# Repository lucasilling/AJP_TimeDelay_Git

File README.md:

# AJP Time Delay Device Documentation

Supplemental material for article on a programmable electronic delay circuit.

- `assembly-instructions`: A guide to ordering parts and building the device
  yourself.

- `arduino/FIFO_P`: The code uploaded to the Arduino Due.

- `fifo-p3f`: The KiCAD files for the device, as well as a schematic
  PDF and the gerber files that I sent for manufacture.

- `program-rescaling`: The code used to calculate the gain and offset
  resistor values to be optimal, given the constraints of E-series
  values and the overall resistances needed.

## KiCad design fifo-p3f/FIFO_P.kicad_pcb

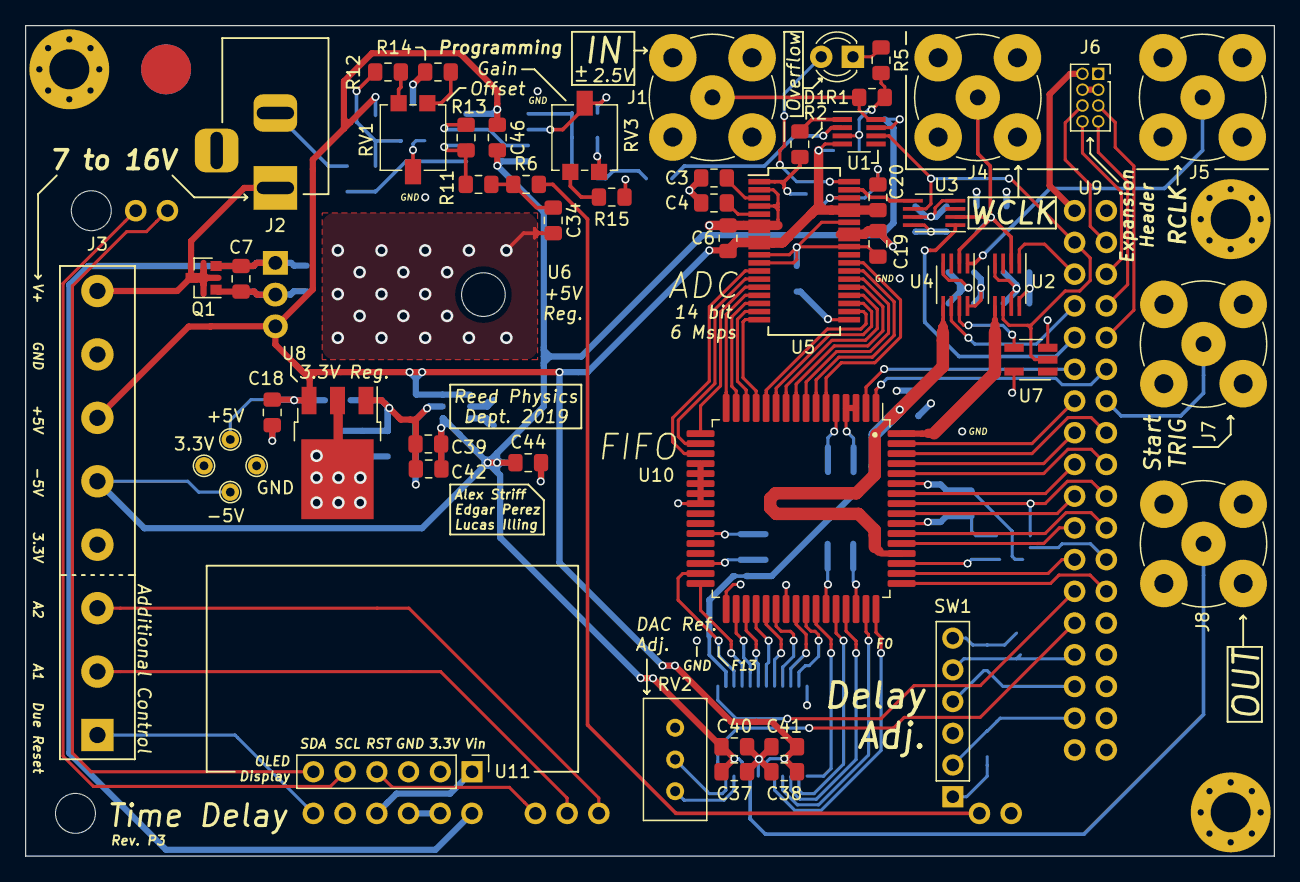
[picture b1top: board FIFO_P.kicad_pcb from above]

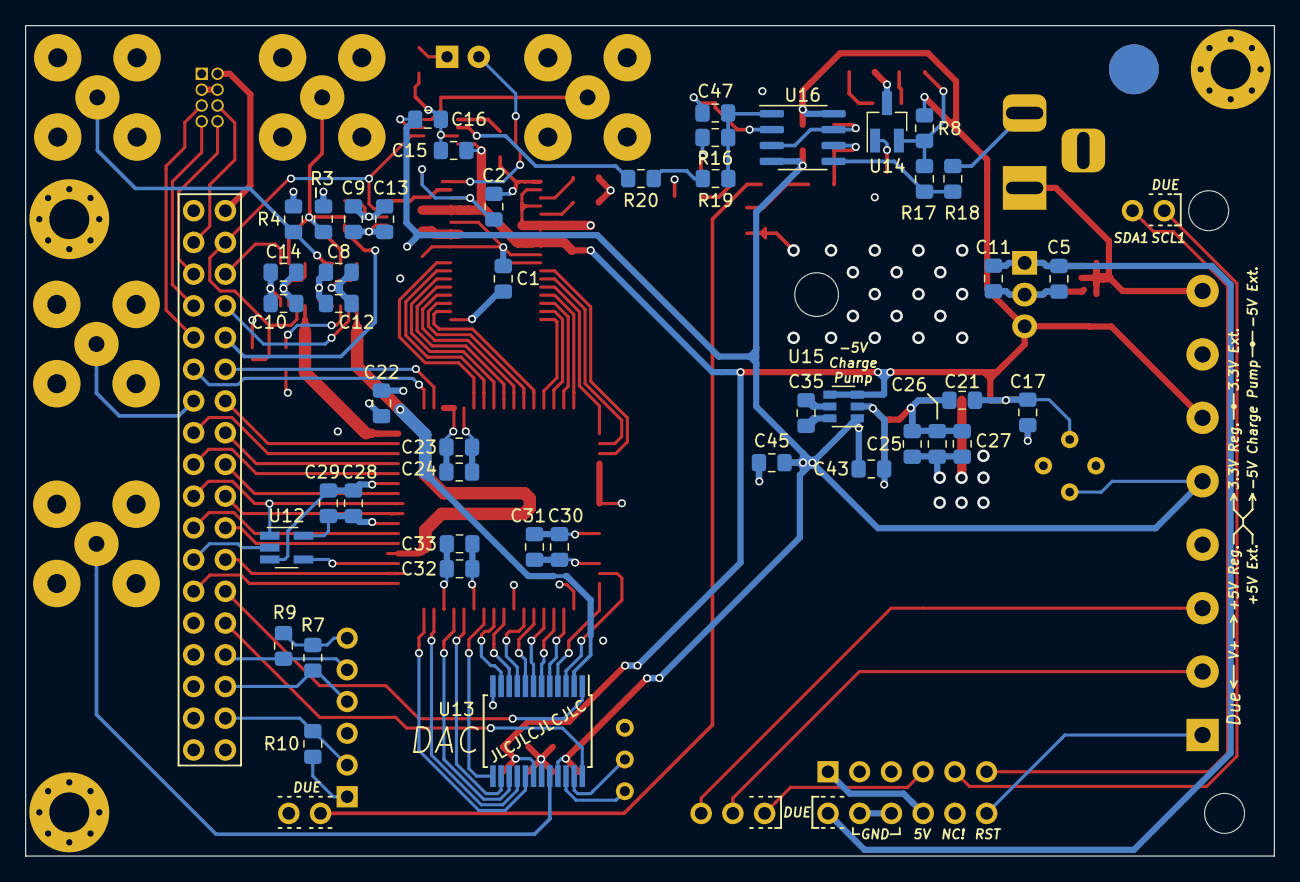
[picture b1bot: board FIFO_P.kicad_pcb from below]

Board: 4 copper layers, 100.0 x 66.5 mm, 100 parts (46 on the bottom side), 104 nets.

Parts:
C1, C3, C4, C6, C11, C12, C13, C14, C19, C20, C21, C25, C35, C39, C40, C41: 1u; C_0805_2012Metric_Pad1.15x1.40mm_HandSolder
C2, C34, C47: 1n; C_0805_2012Metric_Pad1.15x1.40mm_HandSolder
C5, C7, C17, C18, C24, C26, C27, C29, C31, C33, C42, C43, C44, C45: 10u; C_0805_2012Metric_Pad1.15x1.40mm_HandSolder
C8, C9, C10, C15, C16, C22, C23, C28, C30, C32, C37, C38, C46: 0u1; C_0805_2012Metric_Pad1.15x1.40mm_HandSolder
D1: LED_RED; LED_D3.0mm
J1: Vin; BNC_TEConnectivity_1478204_Vertical
J2: Jack-DC; BarrelJack_Horizontal
J3: Screw_Terminal_01x08; TerminalBlock_Phoenix_MKDS-3-8-5.08_1x08_P5.08mm_Horizontal
J4: XWCLK; BNC_TEConnectivity_1478204_Vertical
J5: XRCLK; BNC_TEConnectivity_1478204_Vertical
J6: Conn_02x04_Odd_Even; PinSocket_2x04_P1.27mm_Vertical
J7: Start Trigger; BNC_TEConnectivity_1478204_Vertical
J8: Vout; BNC_TEConnectivity_1478204_Vertical
Q1: DMP3099L; SOT-23
R1, R3, R4, R19: 49R9; R_0805_2012Metric_Pad1.15x1.40mm_HandSolder
R2, R6, R20: 22R; R_0805_2012Metric_Pad1.15x1.40mm_HandSolder
R5: 220R; R_0805_2012Metric_Pad1.15x1.40mm_HandSolder
R7, R9, R10, R11, R13, R16, R17, R18: 5k1; R_0805_2012Metric_Pad1.15x1.40mm_HandSolder
R8, R14: 1k1; R_0805_2012Metric_Pad1.15x1.40mm_HandSolder
R12: 4k3; R_0805_2012Metric_Pad1.15x1.40mm_HandSolder
R15: 3k9; R_0805_2012Metric_Pad1.15x1.40mm_HandSolder
RV1, RV3: 1k; Potentiometer_Vishay_TS53YL_Vertical
RV2: 10k; Potentiometer_Bourns_3296W_Vertical
SW1: Rotary_Encoder_61C
TP1: GND; Test_Pin
TP2: +5V; Test_Pin
TP3: -5V; Test_Pin
TP4: 3.3V; Test_Pin
U1: TS12A12511; SOT-23-8_Handsoldering
U2, U3, U4: SN74LVC2G157_MUX_TI; SSOP-8_2.95x2.8mm_P0.65mm
U5: LTC1740; SSOP-36_5.3mm_Pitch0.65mm
U6: LM2940CT-5.0; TO-220-3_Horizontal_TabDown
U7: 74LVC1G04; SOT-23-5_HandSoldering
U8: LM1117-3.3; TO-252-3_TabPin2
U9: ARDUINO_DUE_FIFO_P_COMMANDS; Arduino_Due_Selected_Pins
U10: IDT_72V2105; LQFP-64_14x14mm_P0.8mm_HandSolder
U11: Adafruit_128x32_OLED_I2C_1306
U12: 74LVC1G08; SOT-23-5_HandSoldering
U13: AD7840; SSOP-24_5.3x8.2mm_P0.65mm
U14: LM4041LP-ADJ; SOT-23_Handsoldering
U15: LM2776; SOT-23-6
U16: TL082; SOIC-8_3.9x4.9mm_P1.27mm

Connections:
1CLK: U4.6, U9.D26
3.3V: C1.2, C8.1, C9.1, C10.1, C12.1, C13.1, C14.1, C22.1, C23.1, C24.1, C25.1, C26.1, C27.1, C28.1, C29.1, C30.1, C31.1, C32.2, C33.2, J3.4, J6.1, R7.1, R9.1, SW1.3, SW1.6, TP4.1, U2.8, U3.8, U4.8, U5.19, U7.5, U8.2, U10.3, U10.4, U10.30, U10.43, U10.55, U12.5
+5V: C6.2, C15.1, C17.1, C18.1, C20.2, C21.1, C38.2, C41.2, C46.1, J3.6, R8.2, TP2.1, U1.4, U5.8, U5.9, U5.32, U5.33, U6.3, U8.3, U13.18, U15.3, U15.4, U16.8
-5V: C16.2, C19.2, C37.1, C39.1, C40.1, C42.1, C43.1, C44.1, C45.1, C46.2, J3.5, TP3.1, U1.7, U5.29, U5.30, U13.21, U15.1, U16.4
/D0: U5.26, U10.6
/D1: U5.25, U10.7
/D2: U5.24, U10.8
/D3: U5.23, U10.9
/D4: U5.22, U10.10
/D5: U5.21, U10.11
/D6: U5.20, U10.12
/D7: U5.18, U10.13
/D8: U5.17, U10.14
/D9: U5.16, U10.15
/D10: U5.15, U10.16
/D11: U5.14, U10.17
/D12: U5.13, U10.18
/D13: U5.12, U10.19
/F0: U10.48, U13.17
/F1: U10.47, U13.16
/F2: U10.45, U13.15
/F3: U10.44, U13.14
/F4: U10.42, U13.13
/F5: U10.41, U13.11
/F6: U10.40, U13.10
/F7: U10.38, U13.9
/F8: U10.37, U13.8
/F9: U10.36, U13.7
/F10: U10.35, U13.6
/F11: U10.34, U13.5
/F12: U10.32, U13.4
/F13: U10.31, U13.3
A1: J3.2, U9.A1
A2: J3.3, U9.A2
ADC_CLK: U3.5, U5.35
ADC_CLK_S: U3.1, U9.D28
GND: C1.1, C2.1, C3.1, C4.2, C5.2, C6.1, C7.2, C8.2, C9.2, C10.2, C11.2, C12.2, C13.2, C14.2, C15.2, C16.1, C17.2, C18.2, C19.1, C20.1, C21.2, C22.2, C23.2, C24.2, C25.2, C26.2, C27.2, C28.2, C29.2, C30.2, C31.2, C32.1, C33.1, C34.2, C37.2, C38.1, C39.2, C40.2, C41.1, C42.2, C43.2, C44.2, C45.2, J1.2, J2.2, J3.7, J4.2, J5.2, J6.3, J6.4, J7.2, J8.2, Q1.1, R1.1, R3.2, R4.2, R5.2, R10.1, R14.2, R15.2, R17.2, RV2.3, SW1.1, TP1.1, U1.3, U2.4, U2.7, U3.4, U3.7, U4.4, U5.2, U5.4, U5.6, U5.7, U5.10, U5.11, U5.28, U5.31, U5.34, U6.2, U7.3, U8.1, U9.GND2, U9.GND3, U10.5, U10.20, U10.21, U10.22, U10.23, U10.24, U10.27, U10.33, U10.39, U10.46, U10.59, U11.3, U12.3, U13.12, U13.19, U14.3, U15.2
unnamed: C2.2, R2.1, U5.1
unnamed: C3.2, U5.3
unnamed: C4.1, U5.5
unnamed: C34.1, R6.1, R11.2
unnamed: C35.1, U15.6
unnamed: C35.2, U15.5
unnamed: C47.1, R16.1, R19.2, U16.1
unnamed: C47.2, RV3.2, U16.2
unnamed: D1.1, R5.1
unnamed: D1.2, U5.36
unnamed: J1.1, R1.2, U1.8
unnamed: J2.1, J3.8, Q1.3
unnamed: J6.2, U9.5V3
unnamed: J6.5, U9.D29
unnamed: J6.6, U9.D23
unnamed: J6.7, U9.D27
unnamed: J6.8, U9.D25
unnamed: J7.1, U9.D33
unnamed: J8.1, U13.20
unnamed: R2.2, U1.1
unnamed: R7.2, SW1.4, U9.D50
unnamed: R9.2, SW1.5, U9.D48
unnamed: R10.2, SW1.2, U9.D52
unnamed: R11.1, R13.2, U16.6
unnamed: R8.1, R12.1, R18.1, U14.2
unnamed: R12.2, RV1.1
unnamed: R13.1, U16.3, U16.7
unnamed: R14.1, RV1.3
unnamed: R15.1, RV3.3
unnamed: R16.2, RV3.1
unnamed: R17.1, R18.2, U16.5
unnamed: R19.1, R20.2
unnamed: RV1.2, U14.1
unnamed: RV2.1, U13.22
unnamed: RV2.2, U13.23
unnamed: U9.D31, U10.1
unnamed: U9.D30, U10.2
unnamed: U9.D45, U10.49
unnamed: U9.D42, U10.50
unnamed: U10.51, U12.4
unnamed: U9.D40, U10.53
unnamed: U9.D41, U10.54
unnamed: U9.D38, U10.56
unnamed: U9.D39, U10.57, U12.1
unnamed: U9.D36, U10.58
unnamed: U9.D37, U10.60
unnamed: U9.D34, U10.61
unnamed: U9.D35, U10.62
unnamed: U9.D32, U10.63
unnamed: U9.5V1, U11.1
unnamed: U9.A0, U11.4
unnamed: U9.SCL1, U11.5
unnamed: U9.SDA1, U11.6
unnamed: U9.D43, U12.2
unnamed: U9.D44, U13.1
unnamed: U9.D46, U13.24
PROG: U4.7, U7.4
PROG_ADC: R20.1, U1.2
PROG_D: R6.2, U9.DAC1
RCLK: U4.5, U10.52, U13.2
RST1: J3.1, U9.RST1
V+: C5.1, C7.1, C11.1, Q1.2, U6.1, U9.VIN
WCLK: U2.5, U10.64
WCLK_S: U2.1, U9.D24
XRCLK: J5.1, R4.1, U4.1
XWCLK: J4.1, R3.1, U2.2, U3.2, U4.2
~PROG: U1.6, U2.6, U3.6, U7.2, U9.D22

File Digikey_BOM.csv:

Manufacturer Part Number,Manufacturer,Digi-Key Part Number,Customer Reference,Reference Designator,Packaging,Part Status,Quantity,Unit Price,Extended Price,Quantity Available,Mfg Std Lead Time,Description,RoHS Status,Lead Free Status,REACH Status
LM2940CT-5.0/NOPB,Texas Instruments,LM2940CT-5.0/NOPB-ND,,U6,Tube,Active,1,1.53,$1.53,7476,6 Weeks,IC REG LINEAR 5V 1A TO220-3,ROHS3 Compliant,Lead free,REACH Unaffected
LM2776DBVR,Texas Instruments,296-43957-1-ND,,U15,Cut Tape (CT),Active,1,1.02,$1.02,12481,6 Weeks,IC REG CHARGE PUMP INV SOT23,ROHS3 Compliant,Lead free,REACH Unaffected
AD7840ARSZ,Analog Devices Inc.,AD7840ARSZ-ND,,U13,Tube,Active,1,33.39,$33.39,643,8 Weeks,IC DAC 14BIT V-OUT 24SSOP,ROHS3 Compliant,Lead free,REACH Unaffected
72V2105L10PFG,Renesas Electronics America Inc.,800-1511-ND,,U10,Tray,Active,1,131.65,$131.65,45,13 Weeks,IC FIFO SUPERSYNC 10NS 64-TQFP,ROHS3 Compliant,Lead free,REACH Unaffected
LTC1740CG#PBF,Linear Technology/Analog Devices,LTC1740CG#PBF-ND,,U5,Tube,Active,1,41.67,$41.67,53,8 Weeks,IC ADC 14BIT PIPELINED 36SSOP,ROHS3 Compliant,Lead free,REACH Unaffected
SN74LVC2G157DCTR,Texas Instruments,296-13266-1-ND,,U2,Cut Tape (CT),Active,3,0.48,$1.44,3725,6 Weeks,IC 2-1LINE DATA SELECT/MUX SM8,ROHS3 Compliant,Lead free,REACH Unaffected
61C11-01-08-02,Grayhill Inc.,GH6102-ND,,SW1,Bulk,Active,1,25.77,$25.77,559,16 Weeks,ROTARY ENCODER OPTICAL 32PPR,RoHS non-compliant,Contains lead,REACH Unaffected
PRPC002SAAN-RC,Sullins Connector Solutions,S1011EC-02-ND,Board to board,U9,Bag,Active,2,0.08,$0.16,34630,Not Available,CONN HEADER VERT 2POS 2.54MM,ROHS3 Compliant,Lead free,REACH Unaffected
PJ-002A,CUI Devices,CP-002A-ND,,J2,Bag,Active,1,0.6,$0.60,35575,11 Weeks,CONN PWR JACK 2X5.5MM SOLDER,RoHS Compliant,Lead free,Not Available
151033RS03000,Würth Elektronik,732-5013-ND,,D1,Bulk,Active,1,0.17,$0.17,13557,14 Weeks,LED RED CLEAR 3MM ROUND T/H,ROHS3 Compliant,Lead free,REACH Unaffected
931,Adafruit Industries LLC,1528-1169-ND,128x32 OLED,U11,Bulk,Active,1,17.5,$17.50,357,2 Weeks,DISPL OLED GRAPH MONO 128X32 I2C,ROHS3 Compliant,Lead free,Not Available
A000062,Arduino,1050-1049-ND,,U9,Box,Active,1,37.4,$37.40,653,Not Available,ARDUINO DUE ATSAM3X8E EVAL BRD,RoHS Compliant,Lead free,Not Available
5-1634503-1,TE Connectivity AMP Connectors,A97581-ND,,"J1, J4, J5, J7, J8",Box,Active,5,2.25,$11.25,11968,Not Available,CONN BNC JACK STR 50 OHM PCB,RoHS Compliant,Lead free,Not Available
TS12A12511DCNR,Texas Instruments,296-27523-1-ND,,U1,Cut Tape (CT),Active,1,1.45,$1.45,11236,6 Weeks,IC SWITCH SGL SPDT ANLG SOT23-8,ROHS3 Compliant,Lead free,REACH Unaffected
LM4041DYM3-ADJ-TR,Microchip Technology,576-2573-1-ND,,U14,Cut Tape (CT),Active,1,0.29,$0.29,2170,4 Weeks,IC VREF SHUNT 10V 1% SOT23-3,ROHS3 Compliant,Lead free,REACH Unaffected
TS53YL102MR10,Vishay Sfernice,TS53YL-1.0KCT-ND,,"RV1, RV3",Cut Tape (CT),Active,2,1.87,$3.74,5901,17 Weeks,TRIMMER 1K OHM 0.25W GW TOP ADJ,ROHS3 Compliant,Lead free,Not Available
DMP3099L-7,Diodes Incorporated,DMP3099L-7DICT-ND,,Q1,Cut Tape (CT),Active,1,0.33,$0.33,183767,23 Weeks,MOSFET P-CH 30V SOT23,ROHS3 Compliant,Lead free,REACH Unaffected
SN74LVC1G04DBVR,Texas Instruments,296-11599-1-ND,,U7,Cut Tape (CT),Active,1,0.32,$0.32,85313,6 Weeks,IC INVERTER 1CH 1-INP SOT23-5,ROHS3 Compliant,Lead free,REACH Unaffected
SN74LVC1G08DBVR,Texas Instruments,296-11601-1-ND,,U12,Cut Tape (CT),Active,1,0.26,$0.26,97419,6 Weeks,IC GATE AND 1CH 2-INP SOT23-5,ROHS3 Compliant,Lead free,REACH Unaffected
08055C104KAT2A,AVX Corporation,478-1395-1-ND,0u1,"C8, C9, C10, C15, C16, C22, C46,C23, C28, C30, C32, C37, C38",Cut Tape (CT),Active,20,0.083,$1.66,36630219,12 Weeks,CAP CER 0.1UF 50V X7R 0805,ROHS3 Compliant,Lead free,REACH Unaffected
08053C105KAT2A,AVX Corporation,478-5030-1-ND,1u,"C1, C3, C4, C6, C19, C20, C40, C41,C11, C12, C13, C14, C21, C25, C35, C39",Cut Tape (CT),Active,20,0.176,$3.52,559518,16 Weeks,CAP CER 1UF 25V X7R 0805,ROHS3 Compliant,Lead free,REACH Unaffected
CL21A106KAYNNNE,Samsung Electro-Mechanics,1276-2891-1-ND,10u,"C5, C7, C17, C18, C26, C27, C42, C43, C44, C45,C24, C29, C31, C33",Cut Tape (CT),Active,20,0.19,$3.80,2116302,22 Weeks,CAP CER 10UF 25V X5R 0805,ROHS3 Compliant,Lead free,REACH Unaffected
08055A102JAT2A,AVX Corporation,478-1328-1-ND,1n,"C2,C34, C47",Cut Tape (CT),Active,10,0.126,$1.26,303649,12 Weeks,CAP CER 1000PF 50V C0G/NP0 0805,ROHS3 Compliant,Lead free,REACH Unaffected
RC0805FR-0749R9L,Yageo,311-49.9CRCT-ND,,"R1, R3, R4, R19",Cut Tape (CT),Active,4,0.1,$0.40,1707550,33 Weeks,RES SMD 49.9 OHM 1% 1/8W 0805,ROHS3 Compliant,Lead free,REACH Unaffected
RC0805FR-0722RL,Yageo,311-22.0CRCT-ND,,"R2, R6, R20",Cut Tape (CT),Active,3,0.1,$0.30,235480,33 Weeks,RES SMD 22 OHM 1% 1/8W 0805,ROHS3 Compliant,Lead free,REACH Unaffected
RC0805FR-07220RL,Yageo,311-220CRCT-ND,,R5,Cut Tape (CT),Active,1,0.1,$0.10,1267440,33 Weeks,RES SMD 220 OHM 1% 1/8W 0805,ROHS3 Compliant,Lead free,REACH Unaffected
RC0805FR-075K1L,Yageo,311-5.10KCRCT-ND,,"R7, R9, R10, R11, R13, R16, R17, R18",Cut Tape (CT),Active,10,0.04,$0.40,2672,33 Weeks,RES SMD 5.1K OHM 1% 1/8W 0805,ROHS3 Compliant,Lead free,REACH Unaffected
RC0805FR-071K1L,Yageo,311-1.10KCRCT-ND,,"R8, R14",Cut Tape (CT),Active,2,0.1,$0.20,745483,33 Weeks,RES SMD 1.1K OHM 1% 1/8W 0805,ROHS3 Compliant,Lead free,REACH Unaffected
RC0805FR-073K9L,Yageo,311-3.90KCRCT-ND,,R15,Cut Tape (CT),Active,1,0.1,$0.10,643670,33 Weeks,RES SMD 3.9K OHM 1% 1/8W 0805,ROHS3 Compliant,Lead free,REACH Unaffected
RC0805FR-074K3L,Yageo,311-4.30KCRCT-ND,,R12,Cut Tape (CT),Active,1,0.1,$0.10,238177,33 Weeks,RES SMD 4.3K OHM 1% 1/8W 0805,ROHS3 Compliant,Lead free,REACH Unaffected
LM1117IDTX-3.3/NOPB,Texas Instruments,LM1117IDTX-3.3/NOPBCT-ND,,U8,Cut Tape (CT),Active,1,1.44,$1.44,21823,6 Weeks,IC REG LINEAR 3.3V 800MA TO252-3,ROHS3 Compliant,Lead free,REACH Unaffected
TL082CDR,Texas Instruments,296-1284-1-ND,,U16,Cut Tape (CT),Active,1,0.41,$0.41,12716,6 Weeks,IC OPAMP JFET 2 CIRCUIT 8SOIC,ROHS3 Compliant,Lead free,REACH Unaffected
OSTTC082162,On Shore Technology Inc.,ED2615-ND,,J3,Bulk,Active,1,1.72,$1.72,1723,8 Weeks,TERM BLK 8P SIDE ENT 5.08MM PCB,ROHS3 Compliant,Lead free,REACH Unaffected
54102-S08-18,Amphenol ICC (FCI),609-5600-ND,Board to board,U9,Bulk,Active,1,1.45,$1.45,197,9 Weeks,CONN HEADER VERT 36POS 2.54MM,RoHS non-compliant,Contains lead,Not Available
PRPC003SAAN-RC,Sullins Connector Solutions,S1011EC-03-ND,Board to board,U9,Bag,Active,1,0.12,$0.12,11543,Not Available,CONN HEADER VERT 3POS 2.54MM,ROHS3 Compliant,Lead free,REACH Unaffected
PRPC006SAAN-RC,Sullins Connector Solutions,S1011EC-06-ND,Board to board,U9,Bag,Active,1,0.19,$0.19,2550,Not Available,CONN HEADER VERT 6POS 2.54MM,ROHS3 Compliant,Lead free,REACH Unaffected
LPPB042CFFN-RC,Sullins Connector Solutions,S9009E-04-ND,Board to board,U9,Tube,Active,1,1.05,$1.05,2828,5 Weeks,CONN HDR 8POS 0.05 GOLD PCB,ROHS3 Compliant,Lead free,REACH Unaffected
RC0805JR-070RL,Yageo,311-0.0ARCT-ND,Jumpers,,Cut Tape (CT),Active,10,0.035,$0.35,11238049,24 Weeks,RES SMD 0 OHM JUMPER 1/8W 0805,ROHS3 Compliant,Lead free,REACH Unaffected
3296W-1-103LF,Bourns Inc.,3296W-103LF-ND,,RV2,Tube,Active,1,2.41,$2.41,4469,6 Weeks,TRIMMER 10K OHM 0.5W PC PIN TOP,ROHS3 Compliant,Lead free,REACH Unaffected

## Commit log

2020-05-18 Create testfike
2020-05-22 Added assembly instructions, removed TeX logs, and reorganized docs
2020-06-01 Use Adafruit 4440 display
